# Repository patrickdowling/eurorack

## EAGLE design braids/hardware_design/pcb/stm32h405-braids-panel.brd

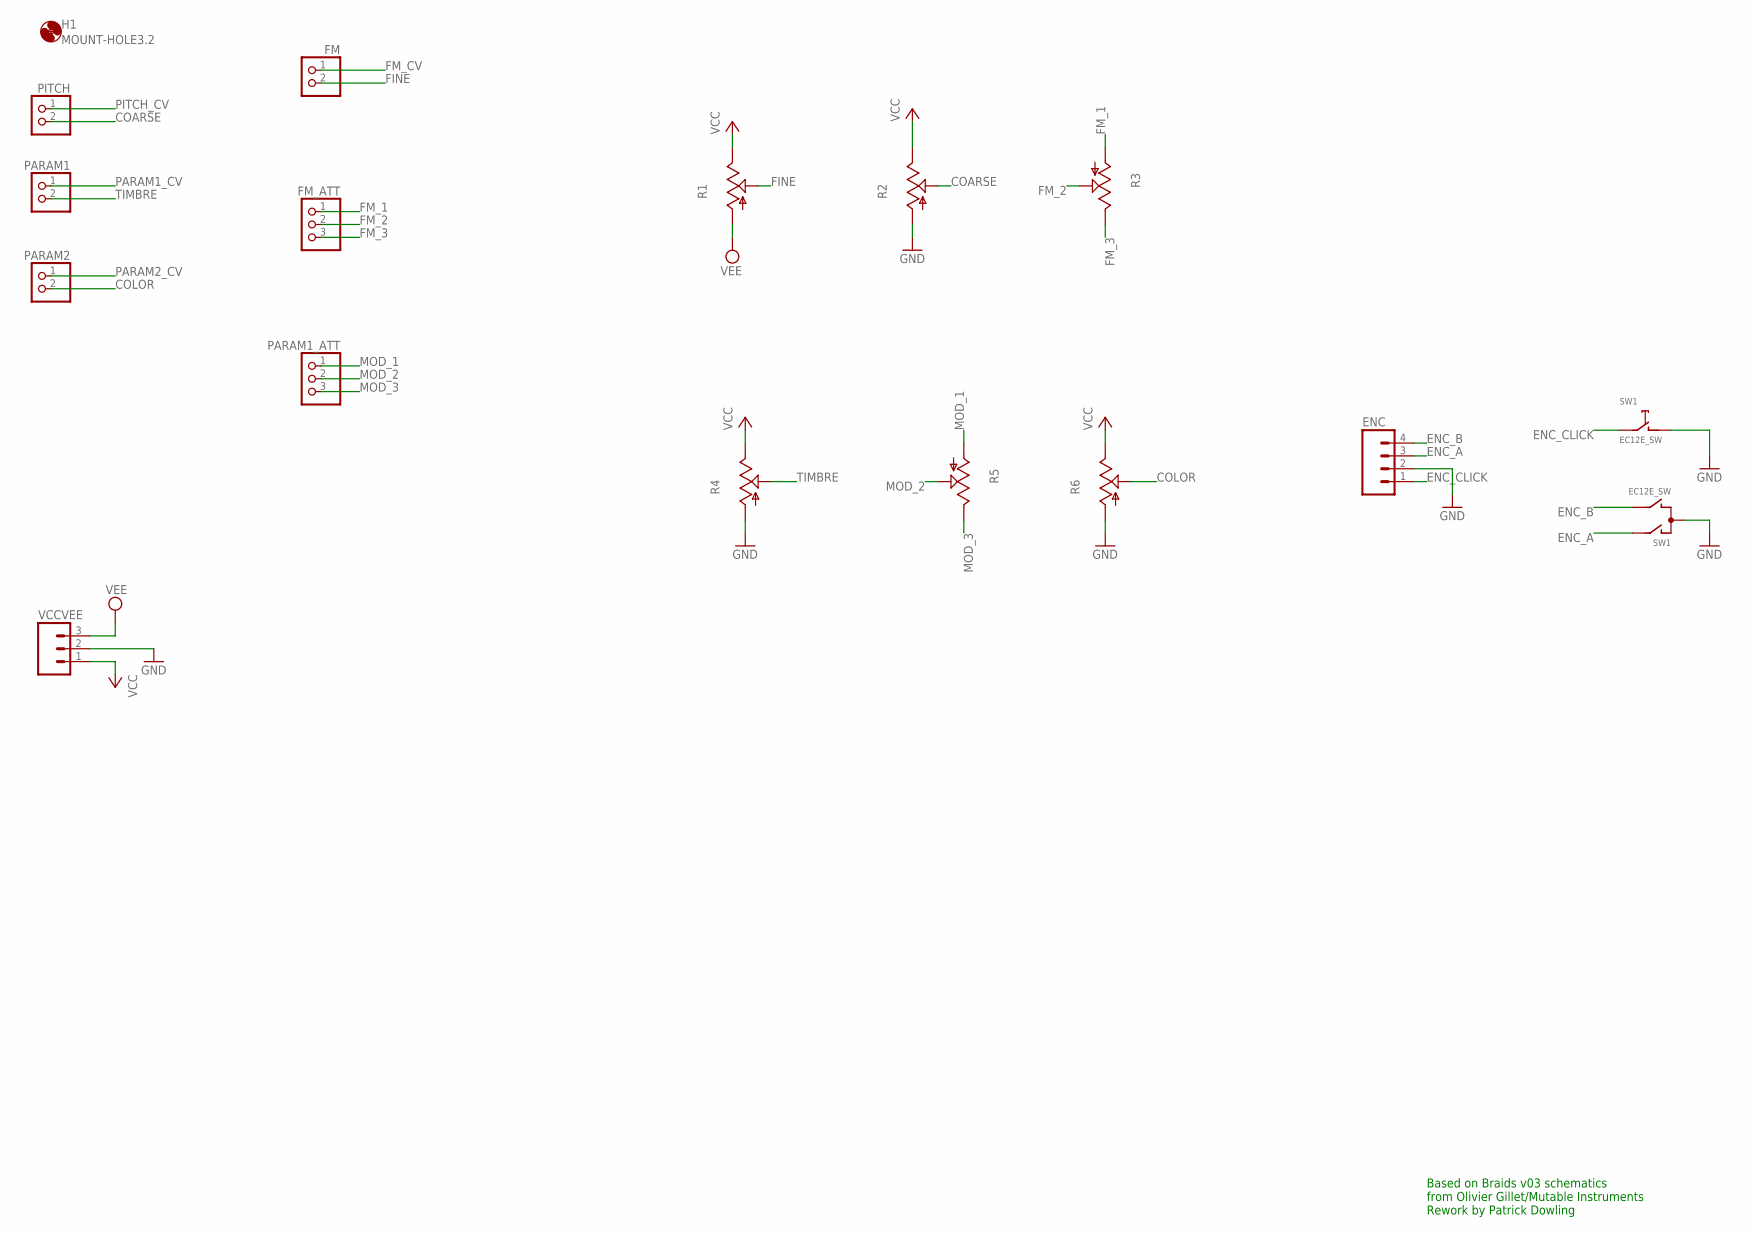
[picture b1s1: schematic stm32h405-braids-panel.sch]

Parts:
ENC: M04PTH; 1X04
FM: PINHD-1X2; 1X02
FM_ATT: PINHD-1X3; 1X03
H1: MOUNT-HOLE3.2; 3,2
PARAM1, PARAM2: PINHD-1X2; 1X02
PARAM1_ATT: PINHD-1X3; 1X03
PITCH: PINHD-1X2; 1X02
R1, R2, R3, R4, R5, R6: POT_USVERTICAL_PS; ALPS_POT_VERTICAL_PS
SW1: EC12E_SW; ALPS_EC12E_SW
VCCVEE: M031X03_NO_SILK; 1X03_NO_SILK

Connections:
COARSE: PITCH.2, R2.P$2 (S)
COLOR: PARAM2.2, R6.P$2 (S)
ENC_A: ENC.3, SW1.A
ENC_B: ENC.4, SW1.B
ENC_CLICK: ENC.1, SW1.E (2)
FINE: FM.2, R1.P$2 (S)
FM_1: FM_ATT.1, R3.P$3 (A)
FM_2: FM_ATT.2, R3.P$2 (S)
FM_3: FM_ATT.3, R3.P$1 (E)
FM_CV: FM.1
GND: ENC.2, R2.P$3 (A), R4.P$3 (A), R6.P$3 (A), SW1.C, SW1.D (1), VCCVEE.2
MOD_1: PARAM1_ATT.1, R5.P$3 (A)
MOD_2: PARAM1_ATT.2, R5.P$2 (S)
MOD_3: PARAM1_ATT.3, R5.P$1 (E)
PARAM1_CV: PARAM1.1
PARAM2_CV: PARAM2.1
PITCH_CV: PITCH.1
TIMBRE: PARAM1.2, R4.P$2 (S)
VCC: R1.P$1 (E), R2.P$1 (E), R4.P$1 (E), R6.P$1 (E), VCCVEE.1
VEE: R1.P$3 (A), VCCVEE.3

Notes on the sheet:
Based on Braids v03 schematics from Olivier Gillet/Mutable Instruments Rework by Patrick Dowling

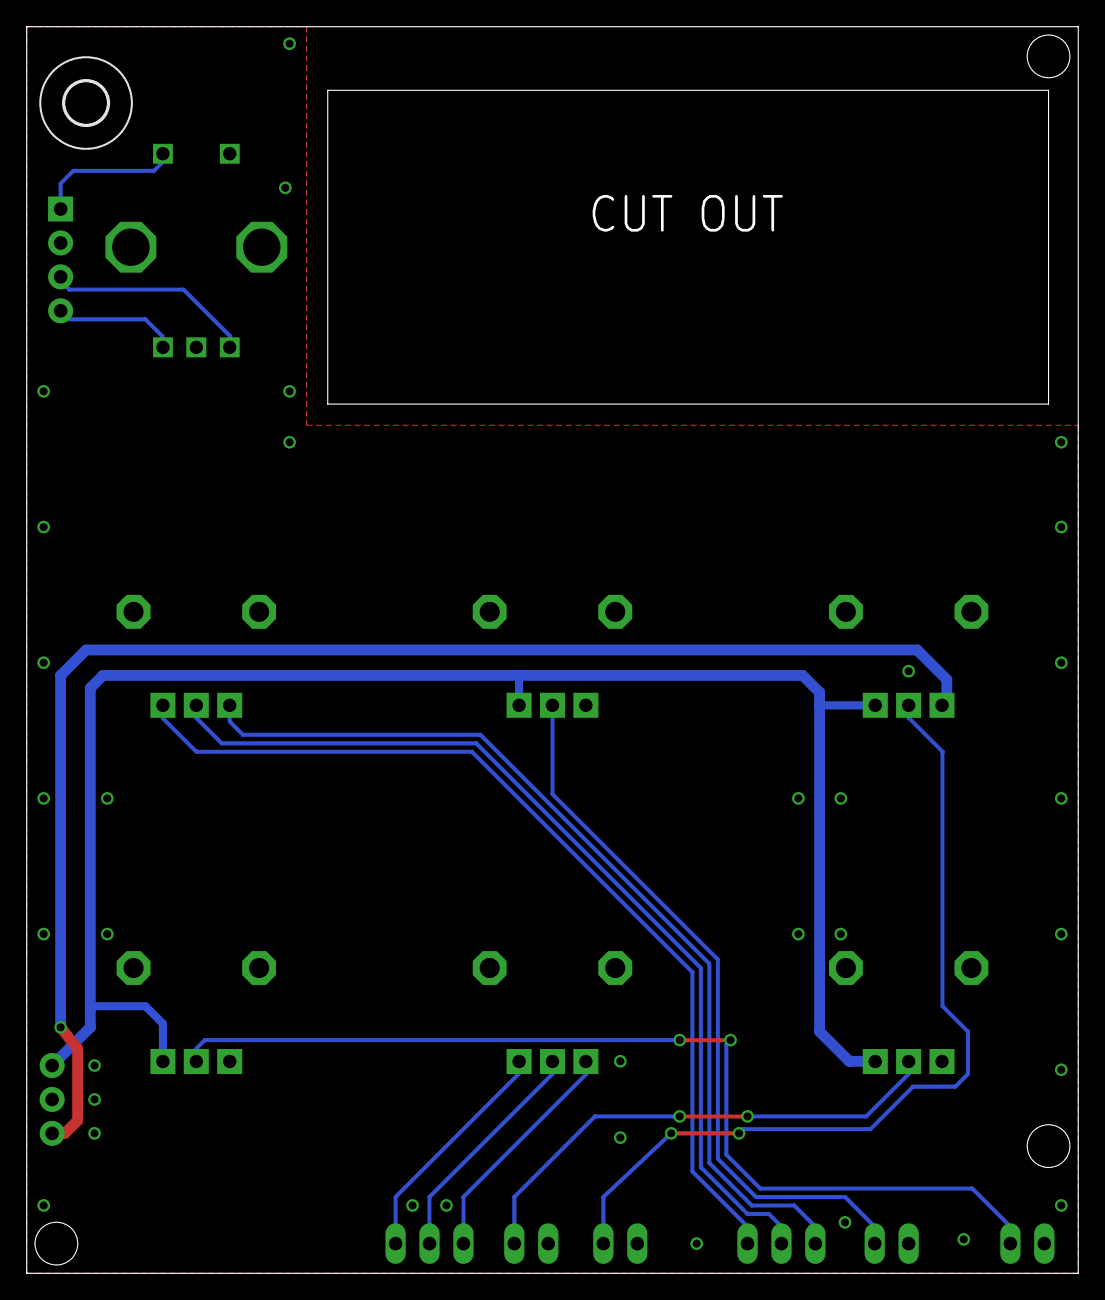
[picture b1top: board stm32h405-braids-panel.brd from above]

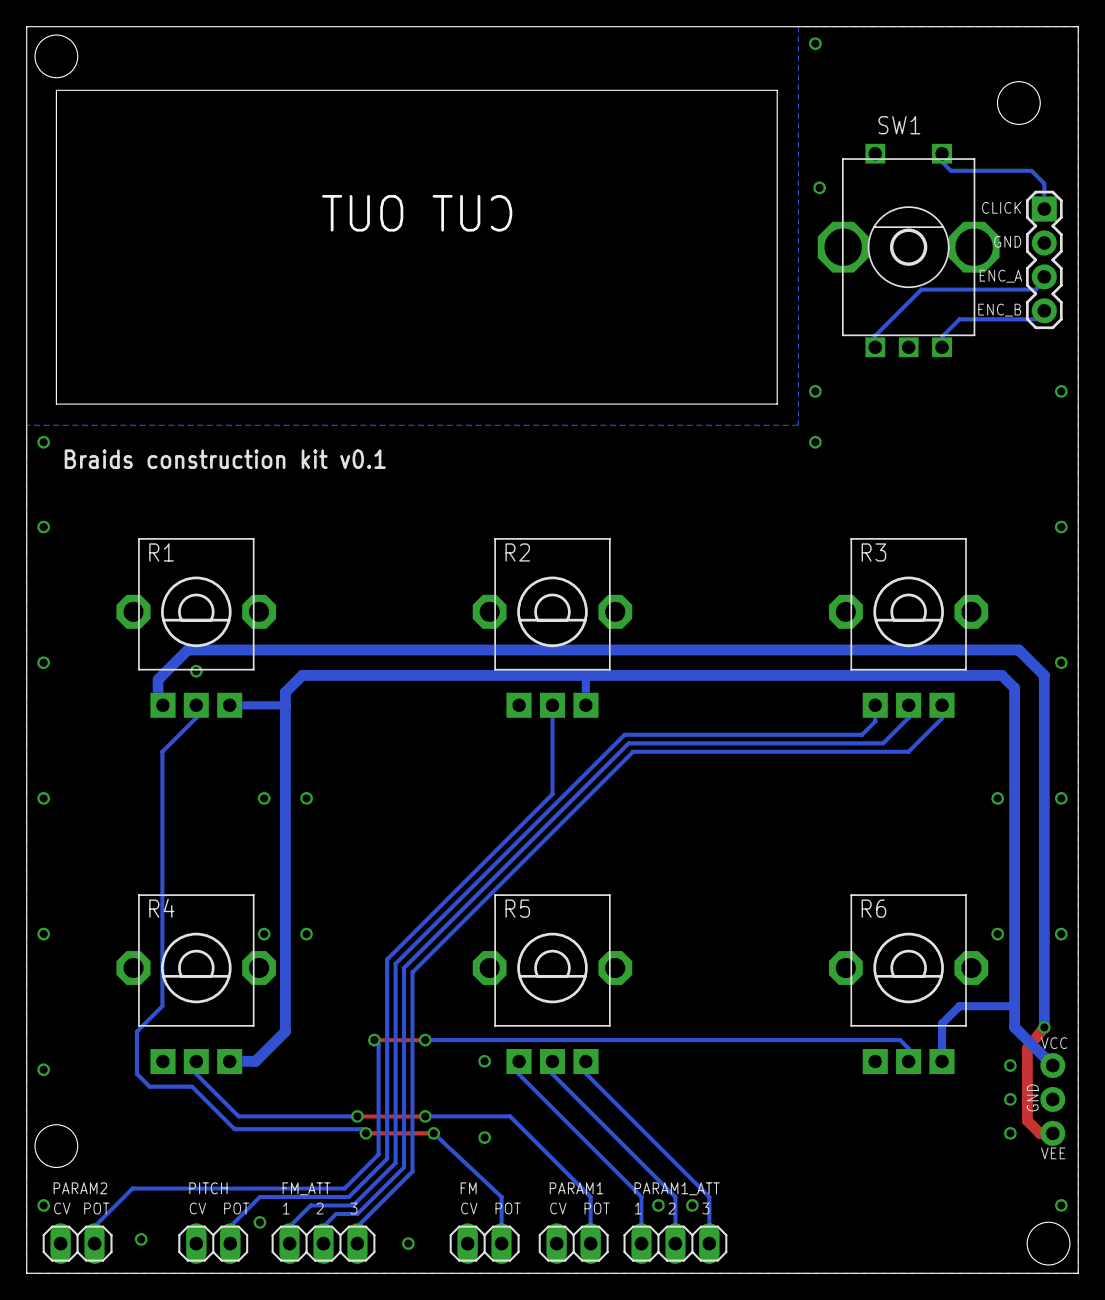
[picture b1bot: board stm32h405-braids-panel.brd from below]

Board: 2 copper layers, 78.7 x 93.3 mm, 16 parts (14 on the bottom side), 16 nets.

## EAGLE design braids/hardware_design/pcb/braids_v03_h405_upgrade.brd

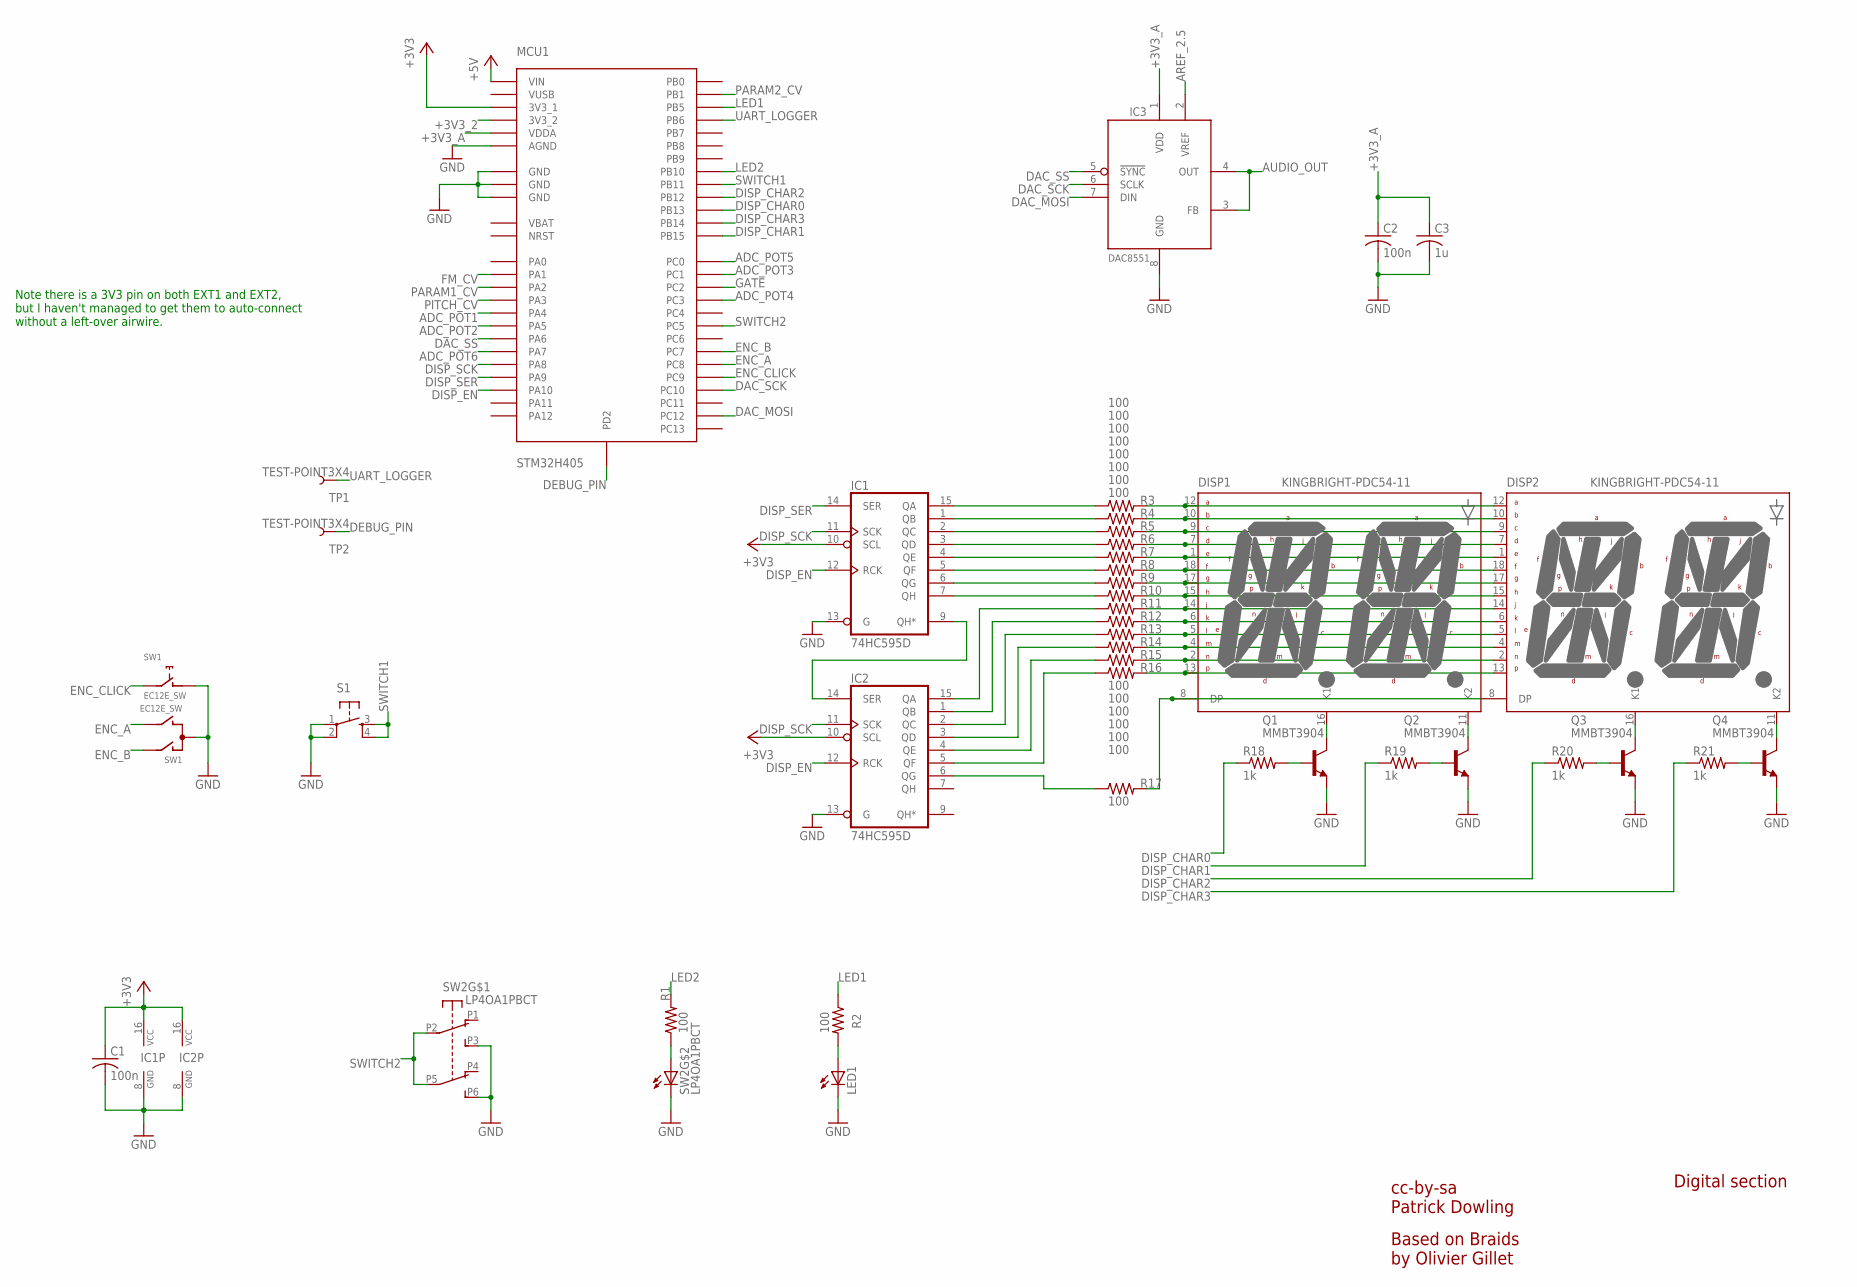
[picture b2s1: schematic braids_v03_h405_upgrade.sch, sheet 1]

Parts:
C1, C2: 100n; C0805
C3: 1u; C0805
DISP1, DISP2: KINGBRIGHT-PDC54-11; PDC54
IC1, IC2: 74HC595D; SO16
IC3: DAC8551; MSOP-8
LED1: LED3MM
MCU1: STM32H405; STM32H103
Q1, Q2, Q3, Q4: MMBT3904; SOT23-BEC
R1: 100; R0805
R2, R3, R4, R5, R6, R7, R8, R9, R10, R11, R12, R13, R14, R15, R16, R17: 100; R0603
R18, R19, R20, R21: 1k; R0603
S1: TAC_SWITCHPTH; TACTILE-PTH
SW1: EC12E_SW; ALPS_EC12E_SW
SW2: LP4OA1PBCT
TP1, TP2: TEST-POINT3X4; PAD.03X.04

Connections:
+3V3: C1.1, IC1.10 (SCL), IC1.16 (VCC), IC2.10 (SCL), IC2.16 (VCC), MCU1.EXT1-5 (3V3_1)
+3V3_2: MCU1.EXT2-5 (3V3_2); also elsewhere on the board
+3V3_A: C2.1, C3.1, IC3.1 (VDD), MCU1.EXT2-1 (VDDA); also elsewhere on the board
+5V: MCU1.EXT2-26 (VIN); also elsewhere on the board
ADC_POT1: MCU1.EXT2-11 (PA4); also elsewhere on the board
ADC_POT2: MCU1.EXT1-18 (PA5); also elsewhere on the board
ADC_POT3: MCU1.EXT1-20 (PC1); also elsewhere on the board
ADC_POT4: MCU1.EXT2-9 (PC3); also elsewhere on the board
ADC_POT5: MCU1.EXT1-19 (PC0); also elsewhere on the board
ADC_POT6: MCU1.EXT1-22 (PA7); also elsewhere on the board
AREF_2.5: IC3.2 (VREF); also elsewhere on the board
AUDIO_OUT: IC3.3 (FB), IC3.4 (OUT); also elsewhere on the board
DAC_MOSI: IC3.7 (DIN), MCU1.EXT1-10 (PC12)
DAC_SCK: IC3.6 (SCLK), MCU1.EXT1-8 (PC10)
DAC_SS: IC3.5 (!SYNC), MCU1.EXT1-14 (PA6)
DEBUG_PIN: MCU1.EXT1-11 (PD2), TP2.P$1
DISP_CHAR0: MCU1.EXT2-16 (PB13), R18.1
DISP_CHAR1: MCU1.EXT2-19 (PB15), R19.1
DISP_CHAR2: MCU1.EXT2-17 (PB12), R20.1
DISP_CHAR3: MCU1.EXT2-18 (PB14), R21.1
DISP_EN: IC1.12 (RCK), IC2.12 (RCK), MCU1.EXT1-7 (PA10)
DISP_SCK: IC1.11 (SCK), IC2.11 (SCK), MCU1.EXT1-2 (PA8)
DISP_SER: IC1.14 (SER), MCU1.EXT1-4 (PA9)
ENC_A: MCU1.EXT2-22 (PC8), SW1.B
ENC_B: MCU1.EXT2-21 (PC7), SW1.A
ENC_CLICK: MCU1.EXT2-24 (PC9), SW1.E (2)
FM_CV: MCU1.EXT2-8 (PA1); also elsewhere on the board
GATE: MCU1.EXT2-2 (PC2); also elsewhere on the board
GND: C1.2, C2.2, C3.2, IC1.8 (GND), IC1.13 (G), IC2.8 (GND), IC2.13 (G), IC3.8 (GND), LED1.K (C), MCU1.EXT1-6 (GND), MCU1.EXT2-3 (AGND), MCU1.EXT2-6 (GND), MCU1.EXT2-25 (GND), Q1.E, Q2.E, Q3.E, Q4.E, S1.1, S1.2, SW1.C, SW1.D (1), SW2.L2, SW2.P3 (A3), SW2.P6 (B3); also elsewhere on the board
LED1: MCU1.EXT1-12 (PB5), R2.1
LED2: MCU1.EXT2-14 (PB10), R1.2
unnamed: DISP1.16 (K1), Q1.C
unnamed: DISP1.11 (K2), Q2.C
unnamed: DISP2.16 (K1), Q3.C
unnamed: DISP2.11 (K2), Q4.C
unnamed: Q1.B, R18.2
unnamed: Q2.B, R19.2
unnamed: Q3.B, R20.2
unnamed: Q4.B, R21.2
unnamed: DISP1.12 (A), DISP2.12 (A), R3.2
unnamed: DISP1.10 (B), DISP2.10 (B), R4.2
unnamed: DISP1.9 (C), DISP2.9 (C), R5.2
unnamed: DISP1.7 (D), DISP2.7 (D), R6.2
unnamed: DISP1.1 (E), DISP2.1 (E), R7.2
unnamed: DISP1.18 (F), DISP2.18 (F), R8.2
unnamed: DISP1.17 (G), DISP2.17 (G), R9.2
unnamed: DISP1.15 (H), DISP2.15 (H), R10.2
unnamed: DISP1.14 (J), DISP2.14 (J), R11.2
unnamed: DISP1.6 (K), DISP2.6 (K), R12.2
unnamed: DISP1.5 (L), DISP2.5 (L), R13.2
unnamed: DISP1.4 (M), DISP2.4 (M), R14.2
unnamed: DISP1.2 (N), DISP2.2 (N), R15.2
unnamed: DISP1.13, DISP2.13, R16.2
unnamed: DISP1.8 (DP), DISP2.8 (DP), R17.2
unnamed: IC1.7 (QH), R10.1
unnamed: IC1.9 (QH*), IC2.14 (SER)
unnamed: IC1.15 (QA), R3.1
unnamed: IC1.1 (QB), R4.1
unnamed: IC1.2 (QC), R5.1
unnamed: IC1.3 (QD), R6.1
unnamed: IC1.4 (QE), R7.1
unnamed: IC1.5 (QF), R8.1
unnamed: IC1.6 (QG), R9.1
unnamed: IC2.15 (QA), R11.1
unnamed: IC2.1 (QB), R12.1
unnamed: IC2.2 (QC), R13.1
unnamed: IC2.3 (QD), R14.1
unnamed: IC2.4 (QE), R15.1
unnamed: IC2.5 (QF), R16.1
unnamed: IC2.6 (QG), R17.1
unnamed: LED1.A, R2.2
unnamed: R1.1, SW2.L1
PARAM1_CV: MCU1.EXT2-7 (PA2); also elsewhere on the board
PARAM2_CV: MCU1.EXT1-26 (PB1); also elsewhere on the board
PITCH_CV: MCU1.EXT2-10 (PA3); also elsewhere on the board
SWITCH1: MCU1.EXT2-15 (PB11), S1.3, S1.4
SWITCH2: MCU1.EXT2-13 (PC5), SW2.P2 (A2), SW2.P5 (B2)
UART_LOGGER: MCU1.EXT1-13 (PB6), TP1.P$1

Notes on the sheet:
cc-by-sa Patrick Dowling
Based on Braids by Olivier Gillet
Digital section
Note there is a 3V3 pin on both EXT1 and EXT2, but I haven't managed to get them to auto-connect without a left-over airwire.

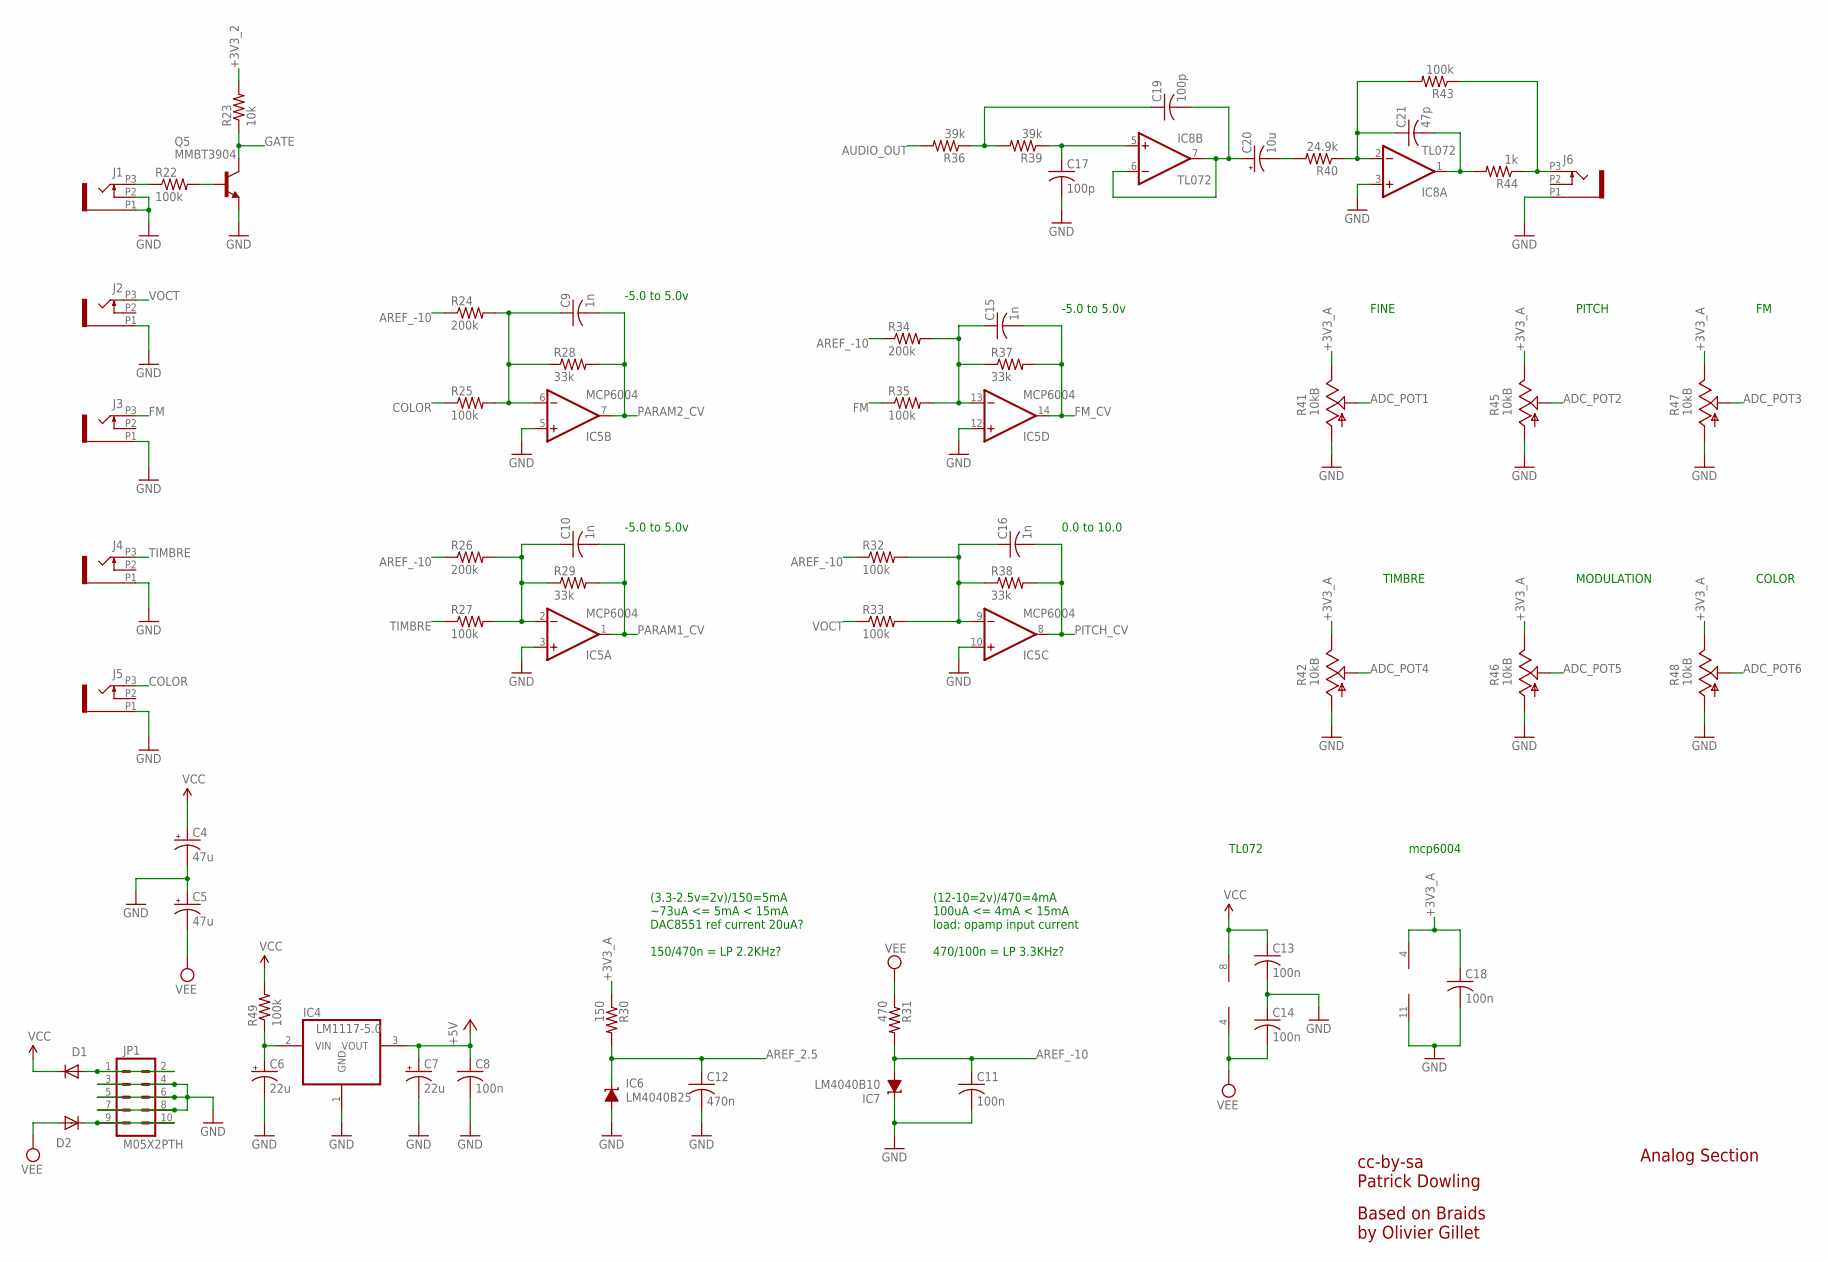
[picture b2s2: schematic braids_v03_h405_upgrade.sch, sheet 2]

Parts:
C4, C5: 47u; PANASONIC_D
C6, C7: 22u; PANASONIC_C
C8, C11, C13, C14, C18: 100n; C0805
C9, C10, C15, C16: 1n; C0805
C12: 470n; C0805
C17, C19: 100p; C0805
C20: 10u; E2-5
C21: 47p; C0805
D1, D2: 1N5819HW; SOD123
IC4: LM1117-5.0; TO252
IC5: MCP6004; SO14
IC6: LM4040B25; DBZ_R-PDSO-G3
IC7: LM4040B10; DBZ_R-PDSO-G3
IC8: TL072; SO08
J1, J2, J3, J4, J5, J6: PJ301_THONKICONN6; WQP_PJ_301M6
JP1: M05X2PTH; AVR_ICSP
Q5: MMBT3904; SOT23-BEC
R22, R25, R27, R32, R33, R35, R43: 100k; R0805
R23: 10k; R0805
R24, R26, R34: 200k; R0805
R28, R29, R37, R38: 33k; R0805
R30: 150; R0805
R31: 470; R0805
R36, R39: 39k; R0805
R40: 24.9k; R0805
R41, R42, R45, R46, R47, R48: 10kB; ALPS_POT_VERTICAL_PS
R44: 1k; R0805
R49: 100k; R1206

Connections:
+3V3_2: R23.2; also elsewhere on the board
+3V3_A: C18.1, IC5.4 (V+), R30.1, R41.P$1 (E), R42.P$1 (E), R45.P$1 (E), R46.P$1 (E), R47.P$1 (E), R48.P$1 (E); also elsewhere on the board
+5V: C7.+, C8.1, IC4.3 (VOUT); also elsewhere on the board
ADC_POT1: R41.P$2 (S); also elsewhere on the board
ADC_POT2: R45.P$2 (S); also elsewhere on the board
ADC_POT3: R47.P$2 (S); also elsewhere on the board
ADC_POT4: R42.P$2 (S); also elsewhere on the board
ADC_POT5: R46.P$2 (S); also elsewhere on the board
ADC_POT6: R48.P$2 (S); also elsewhere on the board
AREF_2.5: C12.1, IC6.1 (C), R30.2; also elsewhere on the board
AREF_-10: C11.1, IC7.2 (A), R24.1, R26.1, R31.2, R32.1, R34.1
AUDIO_OUT: R36.2; also elsewhere on the board
COLOR: J5.P3 (3), R25.1
FM: J3.P3 (3), R35.1
FM_CV: C15.2, IC5.14 (OUT), R37.2; also elsewhere on the board
GATE: Q5.C, R23.1; also elsewhere on the board
GATE_IN: Q5.B, R22.2
GND: C4.-, C5.+, C6.-, C7.-, C8.2, C11.2, C12.2, C13.2, C14.1, C17.2, C18.2, IC4.1 (GND), IC5.3 (+IN), IC5.5 (+IN), IC5.10 (+IN), IC5.11 (V-), IC5.12 (+IN), IC6.2 (A), IC7.1 (C), IC8.3 (+IN), J1.P1 (1), J1.P2 (2), J2.P1 (1), J3.P1 (1), J4.P1 (1), J5.P1 (1), J6.P1 (1), JP1.3, JP1.4, JP1.5, JP1.6, JP1.7, JP1.8, Q5.E, R41.P$3 (A), R42.P$3 (A), R45.P$3 (A), R46.P$3 (A), R47.P$3 (A), R48.P$3 (A); also elsewhere on the board
unnamed: C6.+, IC4.2 (VIN), R49.1
unnamed: D2.C, JP1.9, JP1.10
unnamed: D1.A, JP1.1, JP1.2
unnamed: C9.1, IC5.6 (-IN), R24.2, R25.2, R28.1
unnamed: C15.1, IC5.13 (-IN), R34.2, R35.2, R37.1
unnamed: C10.1, IC5.2 (-IN), R26.2, R27.2, R29.1
unnamed: J1.P3 (3), R22.1
unnamed: C16.1, IC5.9 (-IN), R32.2, R33.2, R38.1
unnamed: C19.2, C20.+, IC8.6 (-IN), IC8.7 (OUT)
unnamed: C20.-, R40.2
unnamed: C17.1, IC8.5 (+IN), R39.1
unnamed: C19.1, R36.1, R39.2
unnamed: J6.P3 (3), R43.1, R44.1
unnamed: C21.2, IC8.1 (OUT), R44.2
unnamed: C21.1, IC8.2 (-IN), R40.1, R43.2
PARAM1_CV: C10.2, IC5.1 (OUT), R29.2; also elsewhere on the board
PARAM2_CV: C9.2, IC5.7 (OUT), R28.2; also elsewhere on the board
PITCH_CV: C16.2, IC5.8 (OUT), R38.2; also elsewhere on the board
TIMBRE: J4.P3 (3), R27.1
VCC: C4.+, C13.1, D1.C, IC8.8 (V+), R49.2
VEE: C5.-, C14.2, D2.A, IC8.4 (V-), R31.1
VOCT: J2.P3 (3), R33.1

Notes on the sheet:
cc-by-sa Patrick Dowling
Based on Braids by Olivier Gillet
Analog Section
mcp6004
0.0 to 10.0
-5.0 to 5.0v
FINE
PITCH
TIMBRE
MODULATION
COLOR
TL072
(12-10=2v)/470=4mA 100uA <= 4mA < 15mA load: opamp input current 470/100n = LP 3.3KHz?
(3.3-2.5v=2v)/150=5mA ~73uA <= 5mA < 15mA DAC8551 ref current 20uA? 150/470n = LP 2.2KHz?

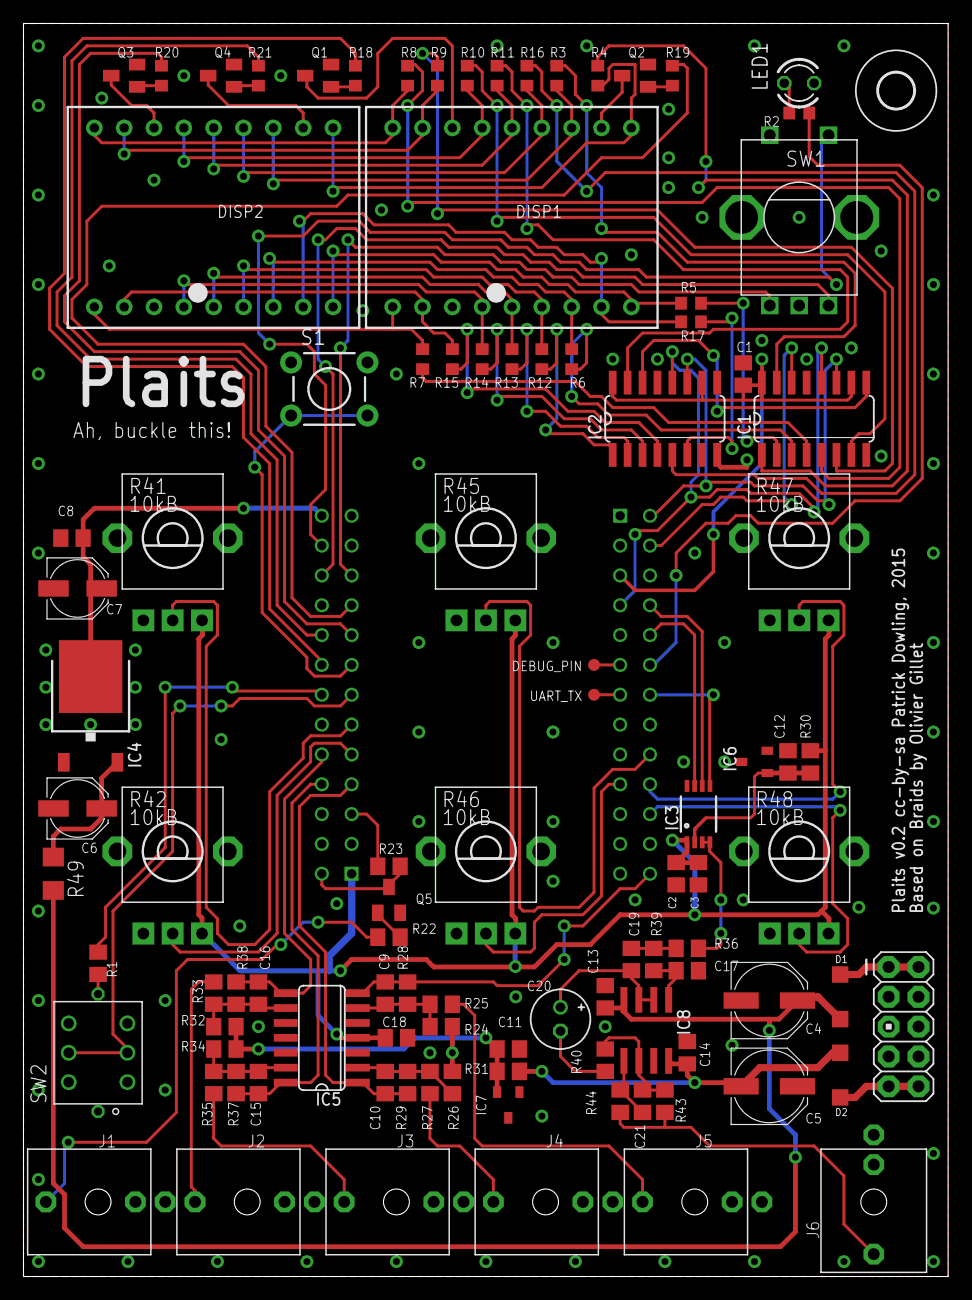
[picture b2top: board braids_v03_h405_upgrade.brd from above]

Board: 2 copper layers, 78.7 x 106.7 mm, 103 parts (1 on the bottom side), 101 nets.

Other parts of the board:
U$1: 3,0
U$2: EURORACK_TEMPLATE

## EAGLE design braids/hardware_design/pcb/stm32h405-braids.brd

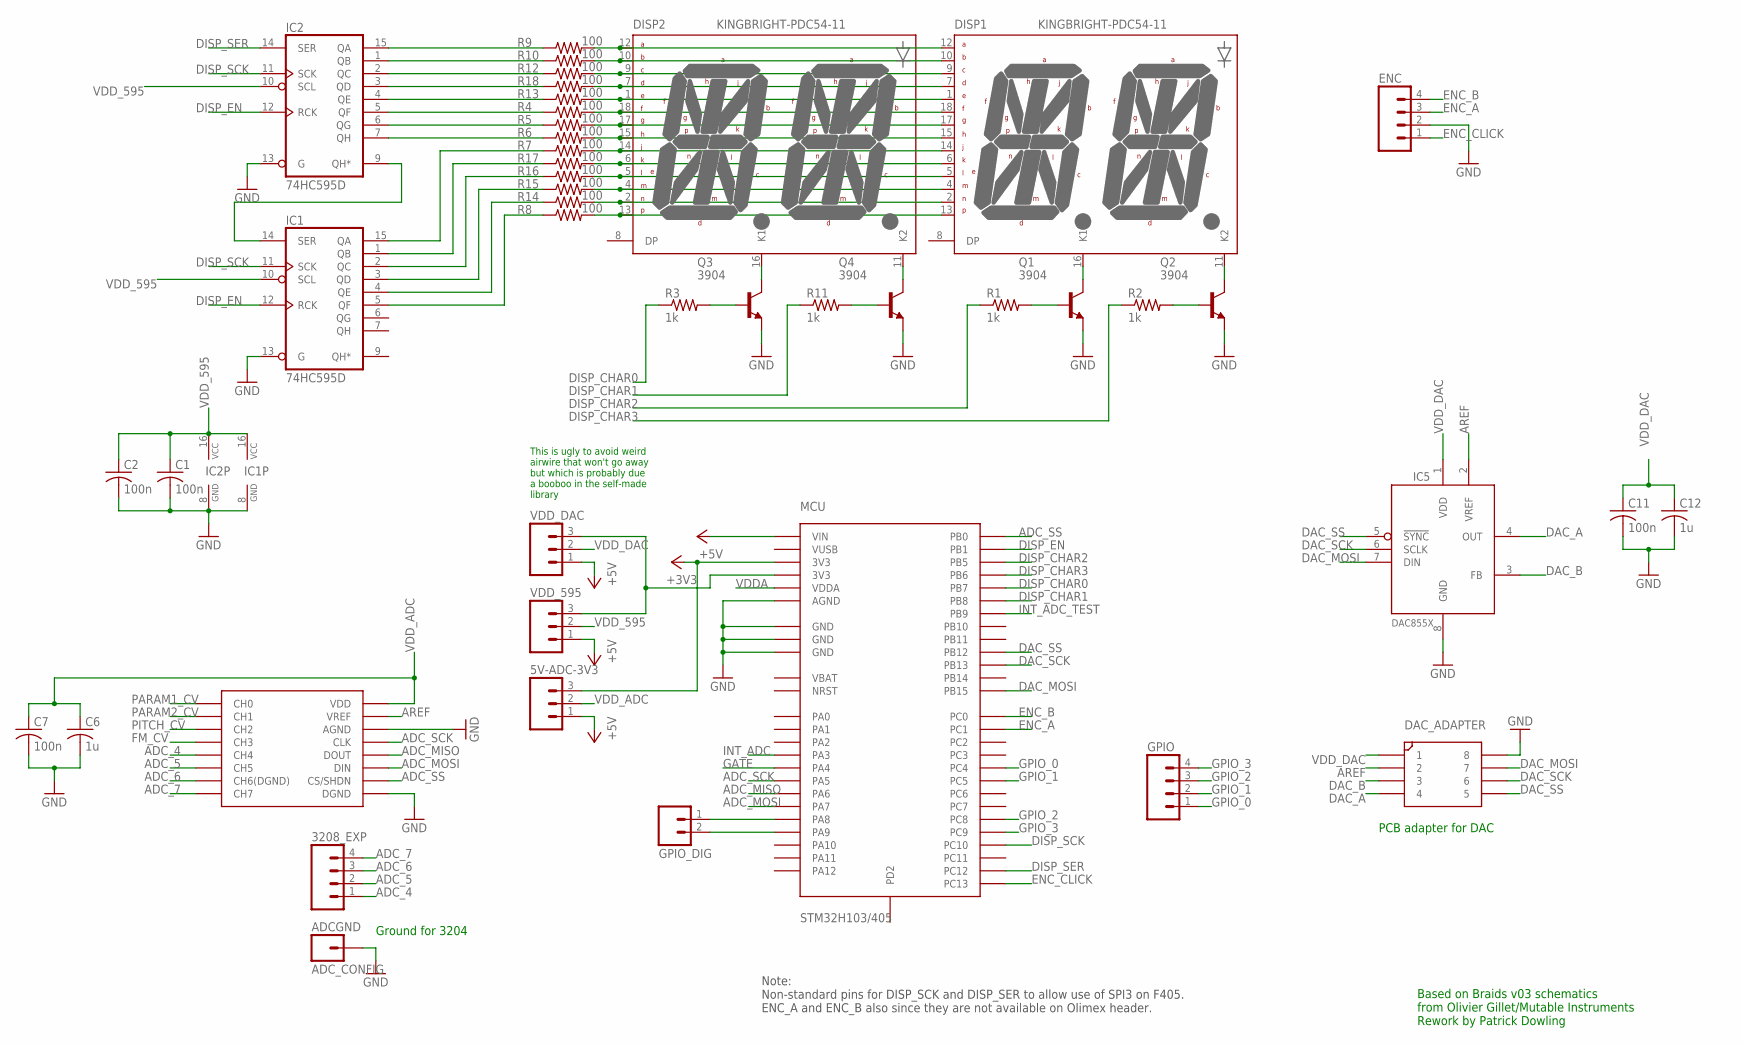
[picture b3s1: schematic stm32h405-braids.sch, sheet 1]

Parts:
5V-ADC-3V3: M031X03_NO_SILK; 1X03_NO_SILK
3208_EXP: M041X04_NO_SILK; 1X04_NO_SILK
ADCGND: ADC_CONFIG; 1X01NS-KIT
C1, C2, C7, C11: 100n; C0805
C6, C12: 1u; C0805
DAC_ADAPTER: DILSOP
DISP1, DISP2: KINGBRIGHT-PDC54-11; PDC54
ENC: M04PTH; 1X04
GPIO: M04NO_SILK_ALL_ROUND; 1X04_NO_SILK_ALL_ROUND
GPIO_DIG: M02PTH; 1X02
IC1, IC2: 74HC595D; SO16
IC4: MCP3204/3208; DIL16
IC5: DAC855X; MSOP-8
MCU: STM32H103/405; STM32H103
Q1, Q2, Q3, Q4: 3904; SOT23-BEC
R1, R2, R3, R11: 1k; R0805
R4, R5, R6, R7, R8, R9, R10, R12, R13, R14, R15, R16, R17, R18: 100; R0603
VDD_595: M031X03_NO_SILK; 1X03_NO_SILK
VDD_DAC: M031X03_NO_SILK; 1X03_NO_SILK

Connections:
+3V3: 5V-ADC-3V3.3, MCU.EXT1-5 (3V3); also elsewhere on the board
+5V: 5V-ADC-3V3.1, MCU.EXT2-26 (VIN), VDD_595.1, VDD_DAC.1; also elsewhere on the board
ADC_4: 3208_EXP.1, IC4.5 (CH4)
ADC_5: 3208_EXP.2, IC4.6 (CH5)
ADC_6: 3208_EXP.3, IC4.7 (CH6(DGND))
ADC_7: 3208_EXP.4, IC4.8 (CH7)
ADC_MISO: IC4.12 (DOUT), MCU.EXT1-14 (PA6)
ADC_MOSI: IC4.11 (DIN), MCU.EXT1-22 (PA7)
ADC_SCK: IC4.13 (CLK), MCU.EXT1-18 (PA5)
ADC_SS: IC4.10 (CS/SHDN), MCU.EXT1-21 (PB0)
AREF: DAC_ADAPTER.P$2 (2), IC4.15 (VREF), IC5.2 (VREF); also elsewhere on the board
DAC_A: DAC_ADAPTER.P$4 (4), IC5.4 (OUT); also elsewhere on the board
DAC_B: DAC_ADAPTER.P$3 (3), IC5.3 (FB); also elsewhere on the board
DAC_MOSI: DAC_ADAPTER.P$7 (7), IC5.7 (DIN), MCU.EXT2-19 (PB15)
DAC_SCK: DAC_ADAPTER.P$6 (6), IC5.6 (SCLK), MCU.EXT2-16 (PB13)
DAC_SS: DAC_ADAPTER.P$5 (5), IC5.5 (!SYNC), MCU.EXT2-17 (PB12)
DISP_CHAR0: MCU.EXT1-15 (PB7), R3.1
DISP_CHAR1: MCU.EXT1-16 (PB8), R11.1
DISP_CHAR2: MCU.EXT1-12 (PB5), R1.1
DISP_CHAR3: MCU.EXT1-13 (PB6), R2.1
DISP_EN: IC1.12 (RCK), IC2.12 (RCK), MCU.EXT1-26 (PB1)
DISP_SCK: IC1.11 (SCK), IC2.11 (SCK), MCU.EXT1-8 (PC10)
DISP_SER: IC2.14 (SER), MCU.EXT1-10 (PC12)
ENC_A: ENC.3, MCU.EXT1-20 (PC1)
ENC_B: ENC.4, MCU.EXT1-19 (PC0)
ENC_CLICK: ENC.1, MCU.EXT1-24 (PC13)
FM_CV: IC4.4 (CH3); also elsewhere on the board
GATE: MCU.EXT2-11 (PA4); also elsewhere on the board
GND: ADCGND.1, C1.2, C2.2, C6.2, C7.2, C11.2, C12.2, DAC_ADAPTER.P$8 (8), ENC.2, IC1.8 (GND), IC1.13 (G), IC2.8 (GND), IC2.13 (G), IC4.9 (DGND), IC4.14 (AGND), IC5.8 (GND), MCU.EXT1-6 (GND), MCU.EXT2-3 (AGND), MCU.EXT2-6 (GND), MCU.EXT2-25 (GND), Q1.E, Q2.E, Q3.E, Q4.E; also elsewhere on the board
GPIO_0: GPIO.1, MCU.EXT2-12 (PC4)
GPIO_1: GPIO.2, MCU.EXT2-13 (PC5)
GPIO_2: GPIO.3, MCU.EXT2-22 (PC8)
GPIO_3: GPIO.4, MCU.EXT2-24 (PC9)
INT_ADC: MCU.EXT2-10 (PA3)
INT_ADC_TEST: MCU.EXT1-17 (PB9)
unnamed: IC1.14 (SER), IC2.9 (QH*)
unnamed: DISP2.16 (K1), Q3.C
unnamed: DISP1.12 (A), DISP2.12 (A), R9.2
unnamed: IC2.15 (QA), R9.1
unnamed: IC2.1 (QB), R10.1
unnamed: IC2.2 (QC), R12.1
unnamed: IC2.3 (QD), R18.1
unnamed: IC2.4 (QE), R13.1
unnamed: IC2.5 (QF), R4.1
unnamed: IC2.6 (QG), R5.1
unnamed: IC2.7 (QH), R6.1
unnamed: IC1.15 (QA), R7.1
unnamed: IC1.1 (QB), R17.1
unnamed: IC1.2 (QC), R16.1
unnamed: IC1.3 (QD), R15.1
unnamed: IC1.4 (QE), R14.1
unnamed: IC1.5 (QF), R8.1
unnamed: DISP1.10 (B), DISP2.10 (B), R10.2
unnamed: DISP1.9 (C), DISP2.9 (C), R12.2
unnamed: DISP1.7 (D), DISP2.7 (D), R18.2
unnamed: DISP1.5 (L), DISP2.5 (L), R16.2
unnamed: DISP1.1 (E), DISP2.1 (E), R13.2
unnamed: DISP1.18 (F), DISP2.18 (F), R4.2
unnamed: DISP1.17 (G), DISP2.17 (G), R5.2
unnamed: DISP1.15 (H), DISP2.15 (H), R6.2
unnamed: DISP1.14 (J), DISP2.14 (J), R7.2
unnamed: DISP1.6 (K), DISP2.6 (K), R17.2
unnamed: DISP1.4 (M), DISP2.4 (M), R15.2
unnamed: DISP1.2 (N), DISP2.2 (N), R14.2
unnamed: DISP1.13, DISP2.13, R8.2
unnamed: Q3.B, R3.2
unnamed: Q4.B, R11.2
unnamed: DISP2.11 (K2), Q4.C
unnamed: DISP1.16 (K1), Q1.C
unnamed: Q1.B, R1.2
unnamed: Q2.B, R2.2
unnamed: DISP1.11 (K2), Q2.C
unnamed: MCU.EXT2-5 (3V3), VDD_595.3, VDD_DAC.3
unnamed: GPIO_DIG.1, MCU.EXT1-2 (PA8)
unnamed: GPIO_DIG.2, MCU.EXT1-4 (PA9)
PARAM1_CV: IC4.1 (CH0); also elsewhere on the board
PARAM2_CV: IC4.2 (CH1); also elsewhere on the board
PITCH_CV: IC4.3 (CH2); also elsewhere on the board
VDDA: MCU.EXT2-1 (VDDA); also elsewhere on the board
VDD_595: C1.1, C2.1, IC1.10 (SCL), IC1.16 (VCC), IC2.10 (SCL), IC2.16 (VCC), VDD_595.2
VDD_ADC: 5V-ADC-3V3.2, C6.1, C7.1, IC4.16 (VDD)
VDD_DAC: C11.1, C12.1, DAC_ADAPTER.P$1 (1), IC5.1 (VDD), VDD_DAC.2

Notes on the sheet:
PCB adapter for DAC
Ground for 3204
Note: Non-standard pins for DISP_SCK and DISP_SER to allow use of SPI3 on F405. ENC_A and ENC_B also since they are not available on Olimex header.
This is ugly to avoid weird airwire that won't go away but which is probably due a booboo in the self-made library
Based on Braids v03 schematics from Olivier Gillet/Mutable Instruments Rework by Patrick Dowling

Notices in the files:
braids/hardware_design/pcb/braids_v03_h405_upgrade.brd:
Plaits v0.2 cc-by-sa Patrick Dowling, 2015
parts and their libraries:
SparkFun-Passives: Licensing: Creative Commons ShareAlike 4.0 International - https://creativecommons.org/licenses/by-sa/4.0
